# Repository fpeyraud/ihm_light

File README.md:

# ihm_light
Basic MMI (IHM) for Tryphon racks

## Description :

Composed of 2 buttons and 4 multi-color LEDs, this interface can be used to
- boot a computer,
- trigger the reset button
- trigger an NMI (short PWON button press)
- trigger a forced shutdown (long PWON button press)
- send button down and button up events to the computer via an USB serial connection
- light LEDs individually or all at once according to commands sent via the USB serial connection

## The hardware
The hardware is composed of an Arduino Pro Micro as [sold by Sparkfun](https://www.sparkfun.com/products/12640) or others on Ebay, coupled to a shield which board and schematics is given in the {board} directory. The shield is a double sided PCB which should be easily realised online.

## The code
The goal has been to stay in the arduino paradigm as much as possible whule providing a complete functionnality with as few blocking functions (delay()) as I could. Oh no it's probably not the best code, but it works pretty well.

## How to use the overall project

When the board is powered up, the leds start scrolling until the serial connection is established.
When established, the board acts on the following commands

* `Lwxyz` : Light leds all at once, wxyz represent the color of each led. It can be set according to the following table:
  * 0 : Off
  * R : Red
  * G : Green
  * B : Blue
  * O : Orange
  * P : Purple
  * C : Cyan
  * W : White
  * r : blinking red
  * g : blinking green
  * b : blinking blue
  * o : blinking orange
  * p : blinking purple
  * c : blinking cyan
  * w : blinking white
* `BRn` : Set brightness from 0 (min) to 15 (max)
* `SLnc` : Light one LED number n with color c as desribed above
* `PWOFF` : Trigger a hard Power Off 
* `RESET` : Trigger the reset button
* `NMI` : Trigger a short PWON press

When the buttons are pressed, L or R are sent on the USB serial port, and l or r are sent when buttons are released.

When both L and R buttons are pressed for 3 seconds, the board enters an internal menu with four options. The currently selected option is represented bu the red LED. Option selection is changed by pressing the L button. The currently option is validated by pressing the R button. The functions for each option is :
1. exit menu
2. NMI
3. RESET
4. Power OFF

When no button is pressed for a certain time after entering the menu, it is automatically exited and LED state is restored as before entering the menu.

## And....

and that's all it does so far. Of course we could add a lot more, but for the time being, it just fits my need ;) Feel free to fork and pull request. Thanks for your attendance ;)

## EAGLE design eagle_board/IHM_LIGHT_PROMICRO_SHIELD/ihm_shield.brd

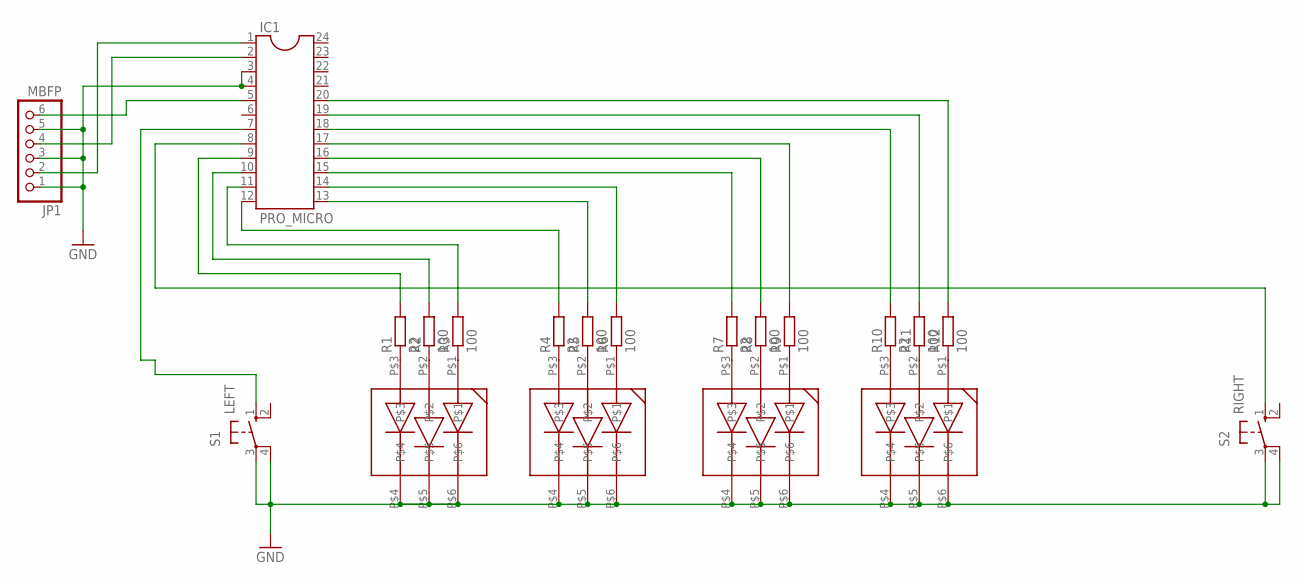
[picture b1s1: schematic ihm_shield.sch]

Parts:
IC1: PRO_MICRO; DIL24-6
JP1: MBFP; 1X06/90
R1, R4, R7, R10: 22; R0805
R2, R3, R5, R6, R8, R9, R11, R12: 100; R0805
S1: LEFT; B3F-10XX
S2: RIGHT; B3F-10XX
U$1, U$2, U$3, U$4: 5050LED; PLCC-6

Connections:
GND: IC1.3, IC1.4, JP1.1, JP1.3, JP1.5, S1.3, S1.4 (P1), S2.3, S2.4 (P1), U$1.P$4, U$1.P$5, U$1.P$6, U$2.P$4, U$2.P$5, U$2.P$6, U$3.P$4, U$3.P$5, U$3.P$6, U$4.P$4, U$4.P$5, U$4.P$6
unnamed: R4.1, U$2.P$3
unnamed: R5.1, U$2.P$2
unnamed: R6.1, U$2.P$1
unnamed: R7.1, U$3.P$3
unnamed: R8.1, U$3.P$2
unnamed: R9.1, U$3.P$1
unnamed: R1.1, U$1.P$3
unnamed: R2.1, U$1.P$2
unnamed: R3.1, U$1.P$1
unnamed: R10.1, U$4.P$3
unnamed: R11.1, U$4.P$2
unnamed: IC1.1, JP1.2
unnamed: IC1.2, JP1.4
unnamed: IC1.5, JP1.6
unnamed: R12.1, U$4.P$1
unnamed: IC1.20, R12.2
unnamed: IC1.19, R11.2
unnamed: IC1.18, R10.2
unnamed: IC1.17, R9.2
unnamed: IC1.16, R8.2
unnamed: IC1.15, R7.2
unnamed: IC1.14, R6.2
unnamed: IC1.13, R5.2
unnamed: IC1.12, R4.2
unnamed: IC1.11, R3.2
unnamed: IC1.10, R2.2
unnamed: IC1.9, R1.2
unnamed: IC1.7, S1.1 (S)
unnamed: IC1.8, S2.1 (S)

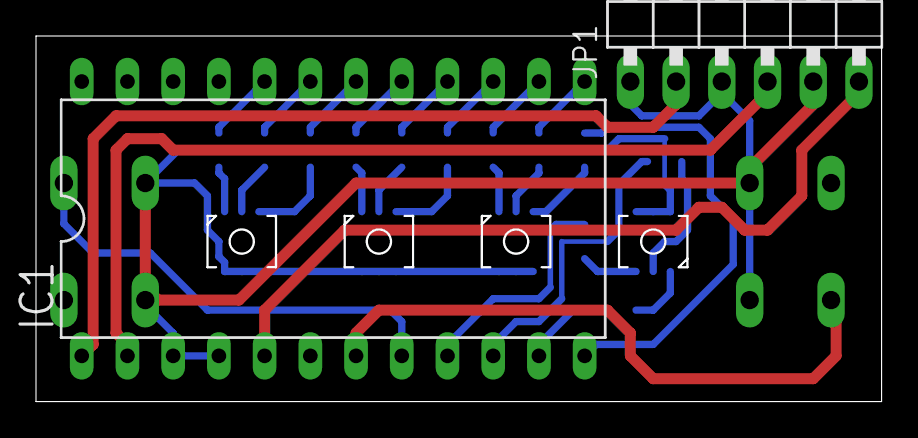
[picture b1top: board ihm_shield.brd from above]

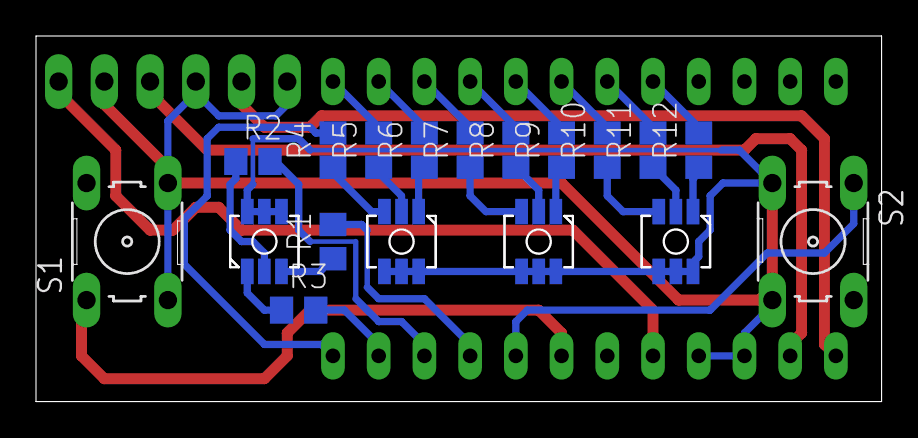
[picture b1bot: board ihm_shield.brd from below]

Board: 2 copper layers, 46.9 x 20.2 mm, 20 parts (18 on the bottom side), 30 nets.

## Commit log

2015-02-01 ready for initial commit
2015-02-01 Added something to read on GitHub
2015-12-27 Code rework to handle RGB leds and pin remapping
2016-01-02 Add brightness control and code refactoring
2016-01-02 update README to reflect last evolutions
